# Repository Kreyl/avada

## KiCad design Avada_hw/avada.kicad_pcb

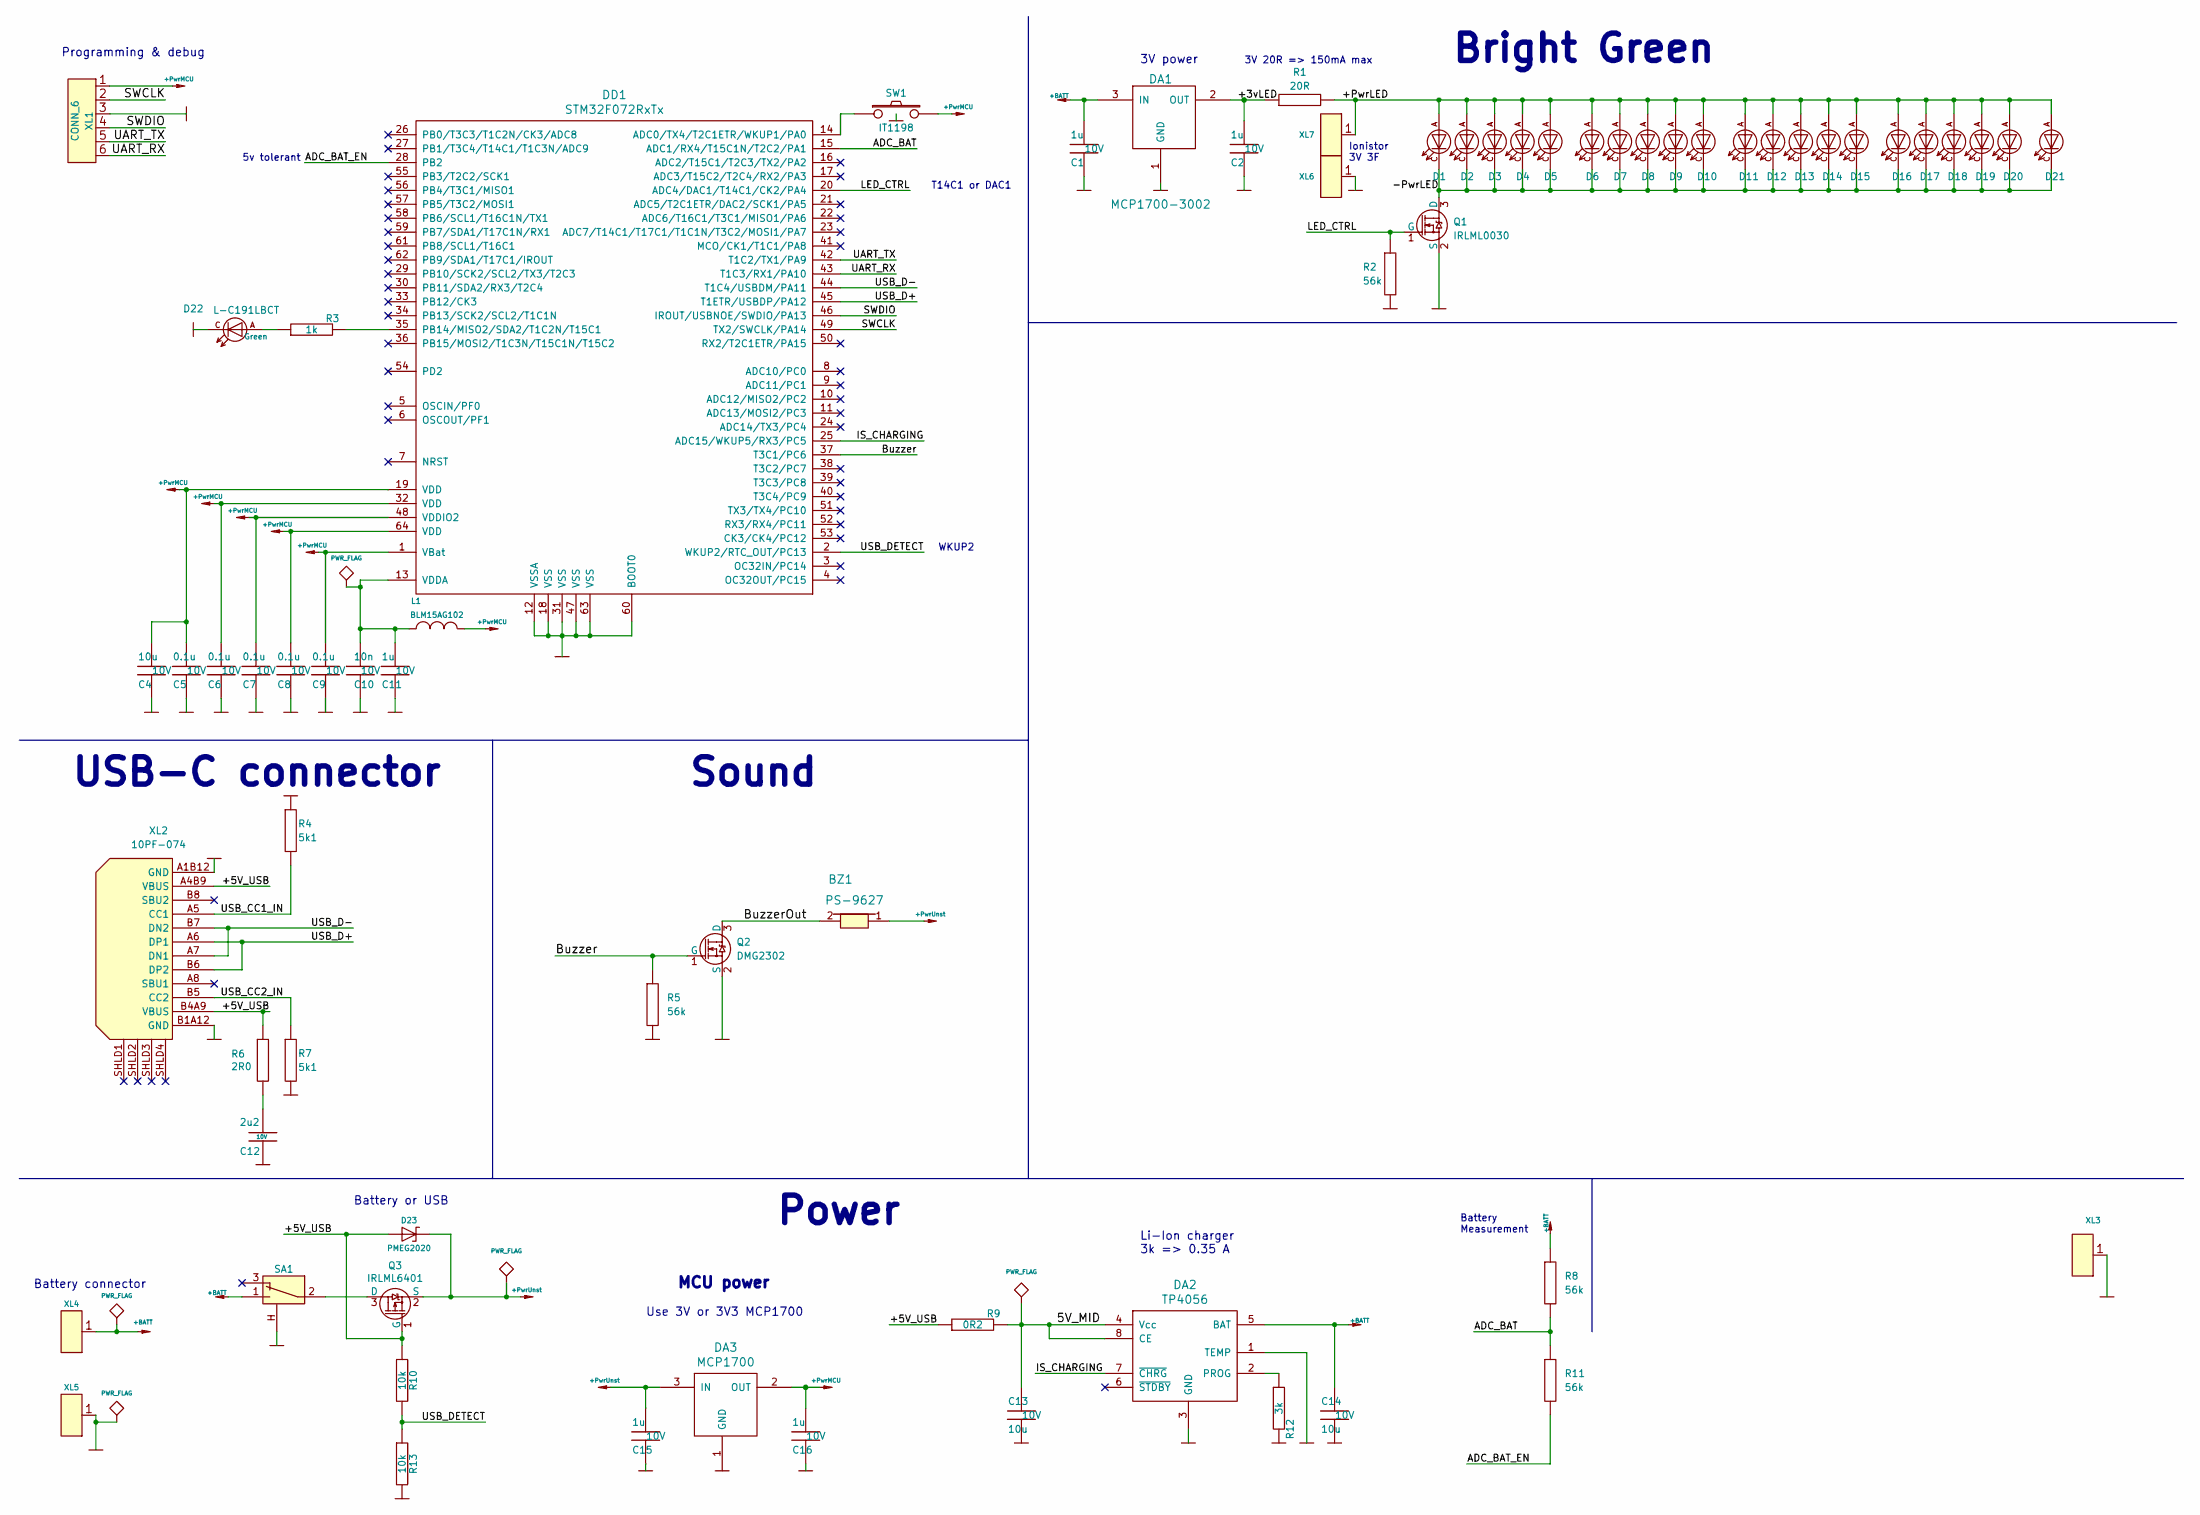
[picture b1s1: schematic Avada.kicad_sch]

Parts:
BZ1: PS-9627; BUZZER_HC0903
C1, C2, C11, C15, C16: 1u; CAP_0603_Silks; Tolerance 20%; Voltage 10V
C4, C13, C14: 10u; CAP_0603_Silks; Tolerance 20%; Voltage 10V
C5, C6, C7, C8, C9: 0.1u; CAP_0603_Silks; Tolerance 20%; Voltage 10V
C10: 10n; CAP_0603_Silks; Tolerance 20%; Voltage 10V
C12: 2u2; CAP_0603_Silks; Tolerance 20%; Voltage 10V
D1, D2, D3, D4, D5, D6, D7, D8, D9, D10, D11, D12, D13, D14, D15, D16, D17, D18, D19, D20, D21: 2835; LED_PLCC2835
D22: L-C191LBCT; LED_0603
D23: PMEG2020; SOD323
DA1: MCP1700-3002; SOT23-3A
DA2: TP4056; SO8_150MIL
DA3: MCP1700; SOT23-3A
DD1: STM32F072RxTx; LQFP64
L1: BLM15AG102; IND_0402; Tolerance 20%
Q1: IRLML0030; SOT23-3
Q2: DMG2302; SOT23-3
Q3: IRLML6401; SOT23-3
R1: 20R; RES_0603; Tolerance 1%
R2, R5, R8, R11: 56k; RES_0603; Tolerance 1%
R3: 1k; RES_0603; Tolerance 1%
R4, R7: 5k1; RES_0603; Tolerance 1%
R6: 2R0; RES_0603; Tolerance 1%
R9: 0R2; RES_1206; Tolerance 1%
R10, R13: 10k; RES_0603; Tolerance 1%
R12: 3k; RES_0603
SA1: SS-12F23; SW_SS-12F23
SW1: IT1198; BTN_IT1198
XL1: CONN_6; PLS-6
XL2: 10PF-074; USBC_10PF-074
XL3, XL5, XL6: CONN_1; PLS-1Square
XL4: CONN_1; PLS-1Oval
XL7: CONN_1; PLS-1Rnd

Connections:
+BATT: C1.1, C14.2, DA1.3 (IN), DA2.5 (BAT), R8.1, SA1.1, XL4.1
+PwrMCU: C4.1, C5.1, C6.1, C7.1, C8.1, C9.1, C16.1, DA3.2 (OUT), DD1.1 (VBat), DD1.19 (VDD), DD1.32 (VDD), DD1.48 (VDDIO2), DD1.64 (VDD), L1.1, SW1.2, XL1.1
+PwrUnst: BZ1.1, C15.1, D23.C, DA3.3 (IN), Q3.2 (S)
/5V_MID: C13.2, DA2.4 (Vcc), DA2.8 (CE), R9.2
/+3vLED: C2.1, DA1.2 (OUT), R1.1
/+5V_USB: D23.A, Q3.1 (G), R6.1, R9.1, R10.1, XL2.A4B9 (VBUS), XL2.B4A9 (VBUS)
/+PwrLED: D1.A, D2.A, D3.A, D4.A, D5.A, D6.A, D7.A, D8.A, D9.A, D10.A, D11.A, D12.A, D13.A, D14.A, D15.A, D16.A, D17.A, D18.A, D19.A, D20.A, D21.A, R1.2, XL7.1
/-PwrLED: D1.C, D2.C, D3.C, D4.C, D5.C, D6.C, D7.C, D8.C, D9.C, D10.C, D11.C, D12.C, D13.C, D14.C, D15.C, D16.C, D17.C, D18.C, D19.C, D20.C, D21.C, Q1.3 (D)
/ADC_BAT: DD1.15 (ADC1/RX4/T15C1N/T2C2/PA1), R8.2, R11.1
/ADC_BAT_EN: DD1.28 (PB2), R11.2
/Buzzer: DD1.37 (T3C1/PC6), Q2.1 (G), R5.1
/BuzzerOut: BZ1.2, Q2.3 (D)
/IS_CHARGING: DA2.7 (~CHRG), DD1.25 (ADC15/WKUP5/RX3/PC5)
/LED_CTRL: DD1.20 (ADC4/DAC1/T14C1/CK2/PA4), Q1.1 (G), R2.1
/SWCLK: DD1.49 (TX2/SWCLK/PA14), XL1.2
/SWDIO: DD1.46 (IROUT/USBNOE/SWDIO/PA13), XL1.4
/UART_RX: DD1.43 (T1C3/RX1/PA10), XL1.6
/UART_TX: DD1.42 (T1C2/TX1/PA9), XL1.5
/USB_CC1_IN: R4.2, XL2.A5 (CC1)
/USB_CC2_IN: R7.1, XL2.B5 (CC2)
/USB_D+: DD1.45 (T1ETR/USBDP/PA12), XL2.A6 (DP1), XL2.B6 (DP2)
/USB_D-: DD1.44 (T1C4/USBDM/PA11), XL2.A7 (DN1), XL2.B7 (DN2)
/USB_DETECT: DD1.2 (WKUP2/RTC_OUT/PC13), R10.2, R13.1
GND: C1.2, C2.2, C4.2, C5.2, C6.2, C7.2, C8.2, C9.2, C10.2, C11.2, C12.2, C13.1, C14.1, C15.2, C16.2, D22.C, DA1.1 (GND), DA2.1 (TEMP), DA2.3 (GND), DA3.1 (GND), DD1.12 (VSSA), DD1.18 (VSS), DD1.31 (VSS), DD1.47 (VSS), DD1.60 (BOOT0), DD1.63 (VSS), Q1.2 (S), Q2.2 (S), R2.2, R4.1, R5.2, R7.2, R12.2, R13.2, SA1.H, SW1.H, XL1.3, XL2.A1B12 (GND), XL2.B1A12 (GND), XL3.1, XL5.1, XL6.1
unnamed: C12.1, R6.2
unnamed: D22.A, R3.1
unnamed: DA2.2 (PROG), R12.1
unnamed: DD1.14 (ADC0/TX4/T2C1ETR/WKUP1/PA0), SW1.1
unnamed: DD1.35 (PB14/MISO2/SDA2/T1C2N/T15C1), R3.2
unnamed: C10.1, C11.1, DD1.13 (VDDA), L1.2
unnamed: Q3.3 (D), SA1.2

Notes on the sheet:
Battery connector
5v tolerant
Programming & debug
Use 3V or 3V3 MCP1700
Battery or USB
MCU power
Ionistor 3V 3F
3V power
Power
USB-C connector
T14C1 or DAC1
Bright Green
3V 20R => 150mA max
Battery Measurement
Li-Ion charger 3k => 0.35 A
WKUP2
Sound

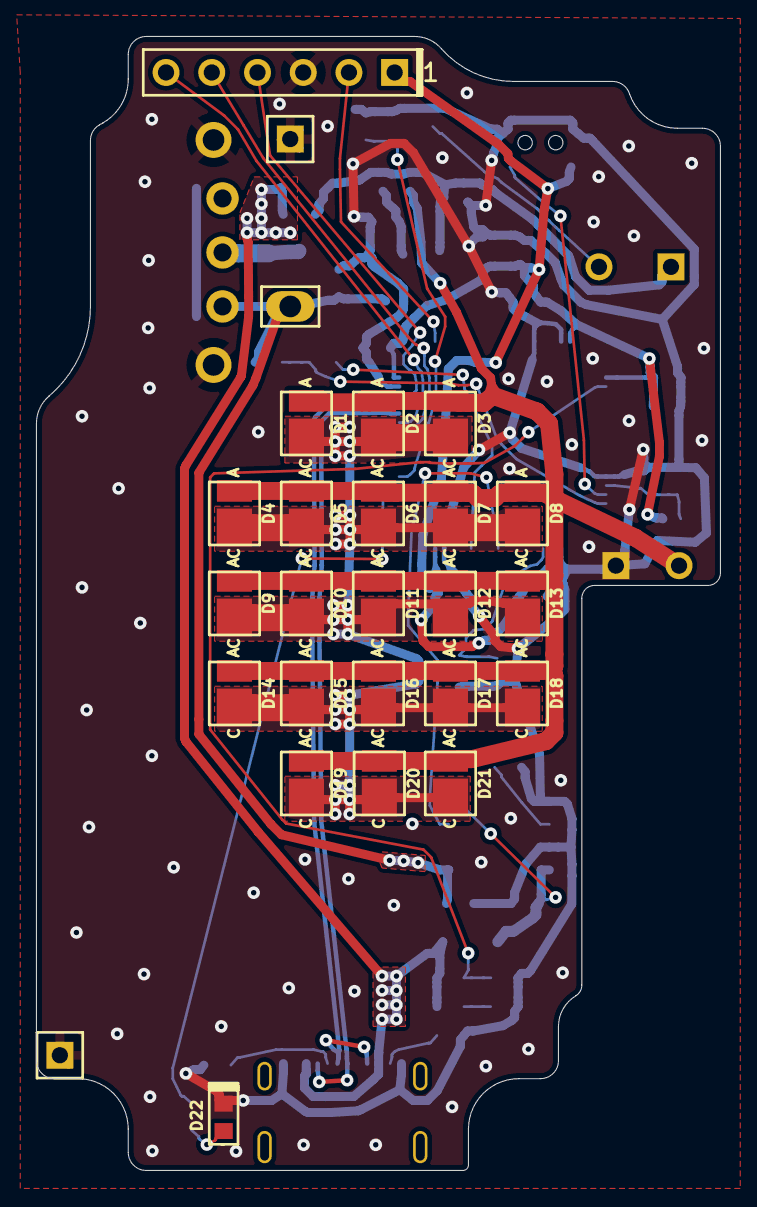
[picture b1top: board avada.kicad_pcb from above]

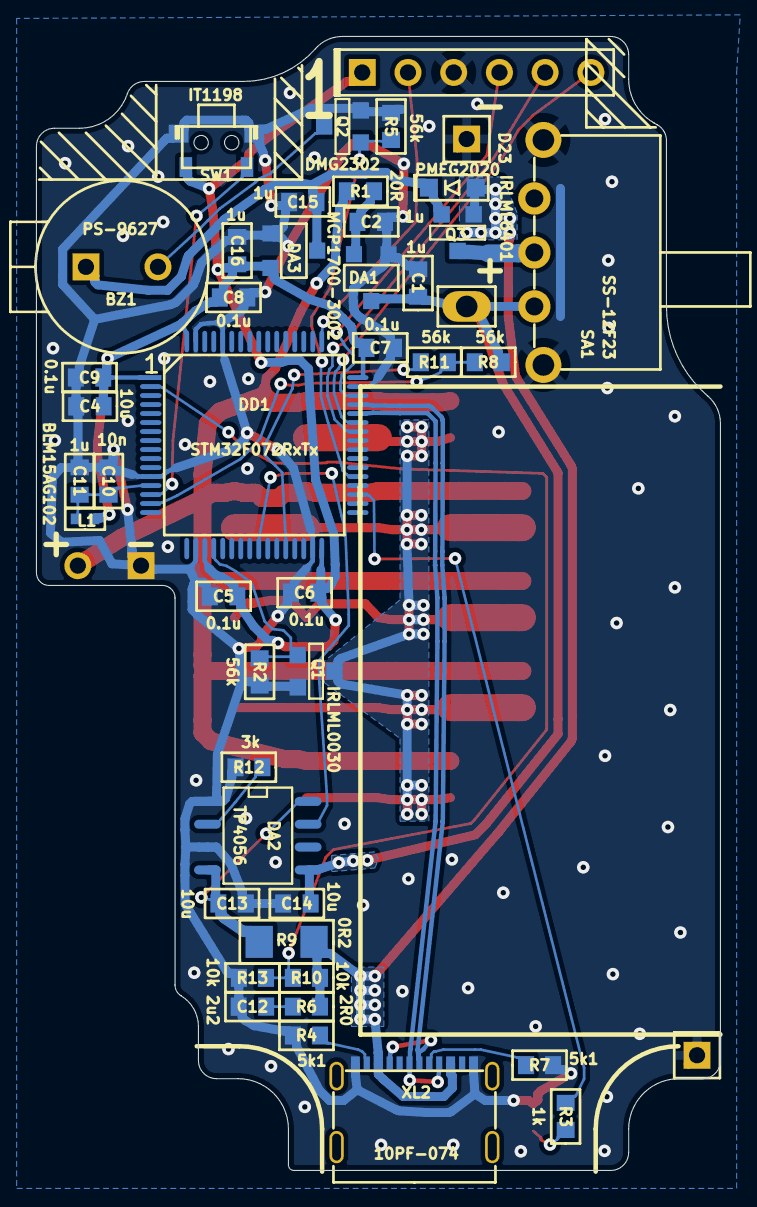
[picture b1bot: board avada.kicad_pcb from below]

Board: 2 copper layers, 38.0 x 63.0 mm, 69 parts (45 on the bottom side), 31 nets.

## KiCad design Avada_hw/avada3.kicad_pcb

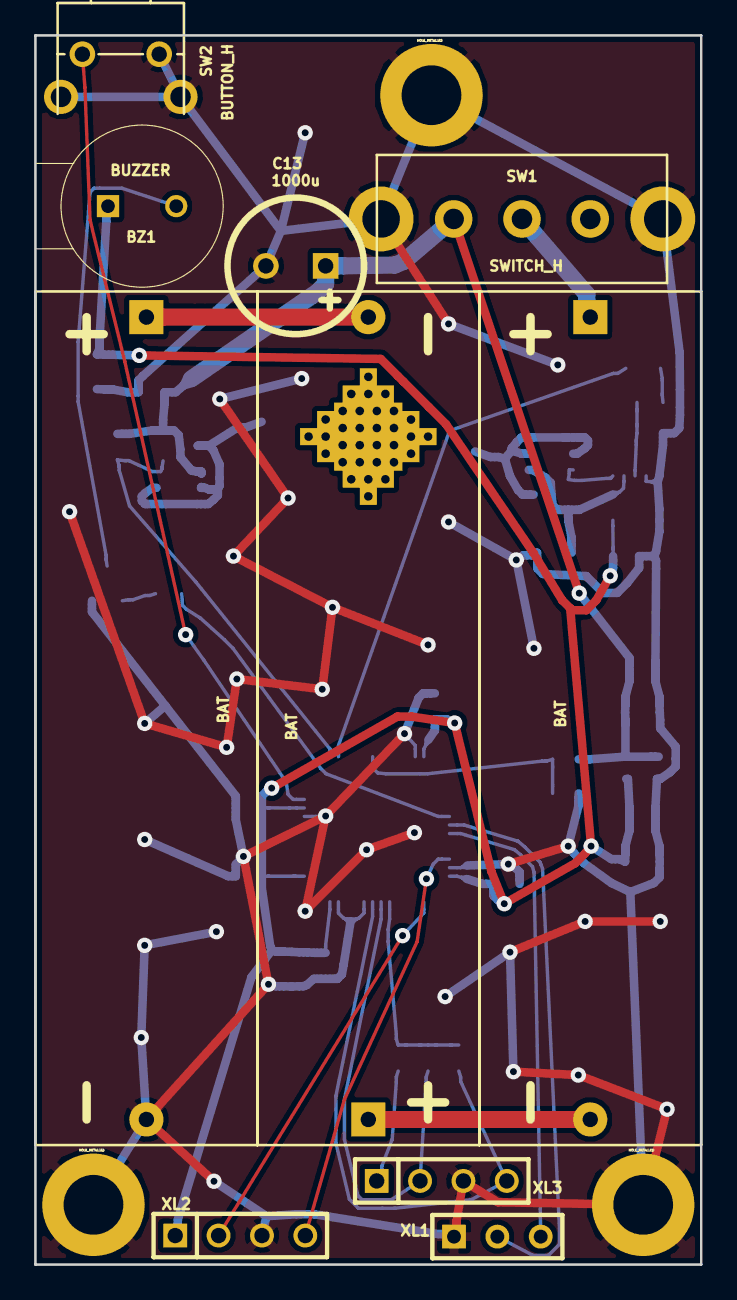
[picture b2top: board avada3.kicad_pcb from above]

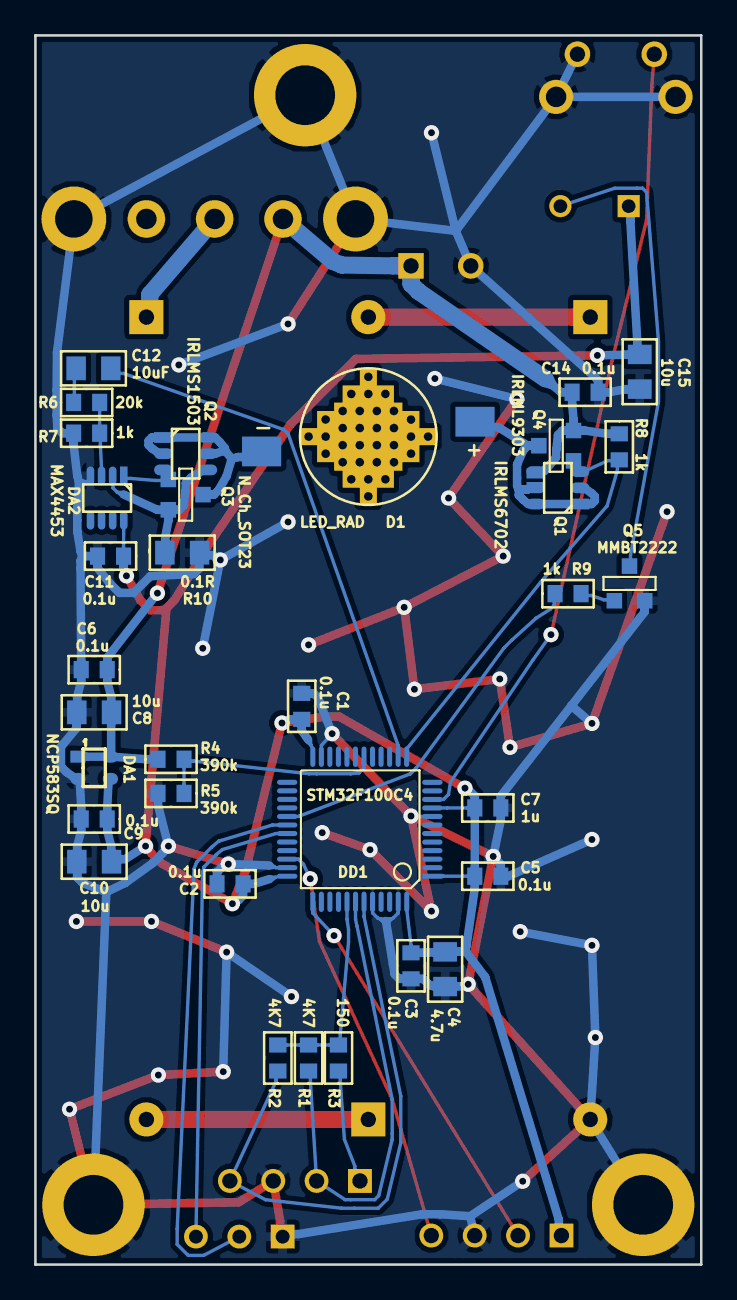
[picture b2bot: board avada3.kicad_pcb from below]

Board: 2 copper layers, 39.0 x 72.0 mm, 47 parts (34 on the bottom side), 27 nets.

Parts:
B1, B2, B3: BAT; BATTERY_AAA_X1
BZ1: BUZZER; BUZZER_HC0903
C1, C2, C3, C5, C6, C9, C11, C14: 0.1u; CAP_0603
C4: 4.7u; CAP_0805
C7: 1u; CAP_0603
C8, C10, C15: 10u; CAP_0805
C12: 10uF; CAP_0805
C13: 1000u; CAP_08xxR
D1: LED_RAD
DA1: NCP583SQ; SC82AB
DA2: MAX4453; SOT23-8
DD1: STM32F100C4; LQFP48
F1: FUSE0R; SOLDERFUSE
HOLE1, HOLE2, HOLE3: HOLE_METALLED; Hole3_5_out6mm
Q1: IRLMS6702; SOT23-6
Q2: IRLMS1503; SOT23-6
Q3: N_Ch_SOT23; SOT23
Q4: IRLML9303; SOT23
Q5: MMBT2222; SOT23
R1, R2: 4K7; RES_0603
R3: 150; RES_0603
R4, R5: 390k; RES_0603
R6: 20k; RES_0603
R7, R8, R9: 1k; RES_0603
R10: 0.1R; RES_0805
SW1: SWITCH_H; SWITCH_SS9
SW2: BUTTON_H; BUTTON_6x6_CORNER
XL1: CONN_3; SIL-3
XL2: ST_SWD; SIL-4
XL3: CONN_4; SIL-4

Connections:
+3.3V: BZ1.1, C1.1, C2.1, C3.1, C4.1, C5.2, C7.1, C9.1, C10.1, C11.1, C15.1, DA1.3, DA2.8, DD1.1, DD1.9, DD1.24, DD1.36, DD1.48, XL2.1
+BATT: C6.1, C8.1, C13.1, C14.1, DA1.1, DA1.4, F1.1, Q1.4, Q4.2, R4.1, R8.1, SW1.1
/BAT_IN: B3.A, SW1.2
/Buzzer: DD1.29, R9.1
/BuzzerOut: BZ1.2, Q5.3
/CURR_SNS: DA2.2, Q2.4, Q3.2, R10.1
/DAC: C12.1, DD1.14
/GreenEn: DD1.13, Q1.3, Q4.1, R8.2
/LED_A: D1.A, F1.2, Q1.1, Q1.2, Q1.5, Q1.6, Q4.3
/LED_C: D1.C, Q2.1, Q2.2, Q2.5, Q2.6, Q3.3
/P_SCL: DD1.42, R1.1, XL3.2
/P_SDA: DD1.43, R2.1, XL3.4
/PeriphPwr: DD1.41, R1.2, R2.2, R3.2
/PeriphPwr1: R3.1, XL3.1
/SWCLK: DD1.37, XL2.2
/SWDIO: DD1.34, XL2.4
/UART_RX: DD1.31, XL1.3
/UART_TX: DD1.30, XL1.2
/UBat/2: DD1.18, R4.2, R5.1
GND: B1.C, C1.2, C2.2, C3.2, C4.2, C5.1, C6.2, C7.2, C8.2, C9.2, C10.2, C11.2, C13.2, C14.2, C15.2, DA1.2, DA2.4, DD1.8, DD1.23, DD1.35, DD1.44, DD1.47, HOLE1.Hle, HOLE2.Hle, HOLE3.Hle, Q5.2, R5.2, R7.2, R10.2, SW1.H, SW2.2, SW2.H, XL1.1, XL2.3, XL3.3
unnamed: B1.A, B2.C
unnamed: Q5.1, R9.2
unnamed: C12.2, R6.1
unnamed: DD1.10, SW2.1
unnamed: B2.A, B3.C
unnamed: DA2.1, Q2.3, Q3.1
unnamed: DA2.3, R6.2, R7.1

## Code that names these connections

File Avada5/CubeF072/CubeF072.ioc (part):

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Mcu.Name=STM32F072R(8-B)Tx
Mcu.Package=LQFP64
Mcu.UserName=STM32F072R8Tx
PA0.Mode=SYS_WakeUp0
PA0.Signal=SYS_WKUP1
PA10.Mode=Asynchronous
PA10.Signal=USART1_RX
PA11.Mode=Device
PA11.Signal=USB_DM
PA12.Mode=Device
PA12.Signal=USB_DP
PA13.Mode=Serial_Wire
PA13.Signal=SYS_SWDIO
PA14.Mode=Serial_Wire
PA14.Signal=SYS_SWCLK
PA2.Mode=IN2
PA2.Signal=ADC_IN2
PA3.Mode=IN3
PA3.Signal=ADC_IN3
PA4.Signal=COMP_DAC1_group
PA9.Mode=Asynchronous
PA9.Signal=USART1_TX
PB14.Signal=S_TIM15_CH1
PC13.Mode=SYS_WakeUp1
PC13.Signal=SYS_WKUP2
PC5.Mode=SYS_WakeUp4
PC5.Signal=SYS_WKUP5
PC6.Signal=S_TIM3_CH1
RCC.SYSCLKFreq_VALUE=48000000
RCC.SYSCLKSource=RCC_SYSCLKSOURCE_HSI48
board=custom

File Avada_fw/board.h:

/*
 * board.h
 *
 *  Created on: 01.02.2017
 *      Author: Kreyl
 */

#pragma once

// ==== General ====
#define BOARD_NAME          "Avada6"
#define APP_NAME            "Avada"

// MCU type as defined in the ST header.
#define STM32F072xB     // no matter, 8 or B

// Freq of external crystal if any. Leave it here even if not used.
#define CRYSTAL_FREQ_HZ         12000000

// Ch timer
#define STM32_ST_IRQ_PRIORITY   2
#define STM32_ST_USE_TIMER      2
#define SYS_TIM_CLK             (Clk.APBFreqHz)

#define SIMPLESENSORS_ENABLED   TRUE
#define BUTTONS_ENABLED         FALSE
#define ADC_REQUIRED            FALSE
#define I2C1_ENABLED            FALSE
#define I2C_USE_SEMAPHORE       FALSE

#if 1 // ========================== GPIO =======================================
// PortMinTim_t: GPIO, Pin, Tim, TimChnl, invInverted, omPushPull, TopValue

// Buttons
#define BTN_PIN         GPIOA, 0, pudPullDown

// LEDs
#define LUMOS_PIN       { GPIOB, 14, TIM15, 1, invNotInverted, omPushPull, 255 }
#define GREEN_LED       GPIOA, 4

// Battery
#define IS_CHARGING     GPIOC, 5, pudPullUp

// Buzzer
#define BUZZER_PIN      GPIOC, 6, TIM3, 1, invNotInverted, omPushPull, 45

// UART
#define UART_GPIO       GPIOA
#define UART_TX_PIN     9
#define UART_RX_PIN     10

// USB
#define USB_DETECT_PIN  GPIOC, 13
#define USB_DM          GPIOA, 11
#define USB_DP          GPIOA, 12

#endif // GPIO

#if 1 // ========================== USB ========================================
#define USBDrv          USBD1   // USB driver to use

// CRS
#define CRS_PRESCALER   RCC_CRS_SYNC_DIV1
#define CRS_SOURCE      RCC_CRS_SYNC_SOURCE_USB
#define CRS_POLARITY    RCC_CRS_SYNC_POLARITY_RISING
#define CRS_RELOAD_VAL  ((48000000 / 1000) - 1) // Ftarget / Fsync - 1
#define CRS_ERROR_LIMIT 34
#define HSI48_CALIBRATN 32
#endif

#if 1 // =========================== DMA =======================================
#define STM32_DMA_REQUIRED  TRUE
// ==== Uart ====
#define UART_DMA_TX_MODE(Chnl) (STM32_DMA_CR_CHSEL(Chnl) | DMA_PRIORITY_LOW | STM32_DMA_CR_MSIZE_BYTE | STM32_DMA_CR_PSIZE_BYTE | STM32_DMA_CR_MINC | STM32_DMA_CR_DIR_M2P | STM32_DMA_CR_TCIE)
#define UART_DMA_RX_MODE(Chnl) (STM32_DMA_CR_CHSEL(Chnl) | DMA_PRIORITY_MEDIUM | STM32_DMA_CR_MSIZE_BYTE | STM32_DMA_CR_PSIZE_BYTE | STM32_DMA_CR_MINC | STM32_DMA_CR_DIR_P2M | STM32_DMA_CR_CIRC)
#define UART_DMA_TX     STM32_DMA_STREAM_ID(1, 2)
#define UART_DMA_RX     STM32_DMA_STREAM_ID(1, 3)
#define UART_DMA_CHNL   0   // Dummy

#if ADC_REQUIRED
#define ADC_DMA         STM32_DMA_STREAM_ID(1, 1)
#define ADC_DMA_MODE    STM32_DMA_CR_CHSEL(0) |   /* dummy */ \
                        DMA_PRIORITY_HIGH | \
                        STM32_DMA_CR_MSIZE_HWORD | \
                        STM32_DMA_CR_PSIZE_HWORD | \
                        STM32_DMA_CR_MINC |       /* Memory pointer increase */ \
                        STM32_DMA_CR_DIR_P2M |    /* Direction is peripheral to memory */ \
                        STM32_DMA_CR_TCIE         /* Enable Transmission Complete IRQ */
#endif // ADC

#endif // DMA

#if 1 // ========================== USART ======================================
#define PRINTF_FLOAT_EN FALSE
#define UART_TXBUF_SZ   2048
#define UART_RXBUF_SZ   512
#define CMD_BUF_SZ      256

#define CMD_UART        USART1


#define CMD_UART_PARAMS \
    CMD_UART, UART_GPIO, UART_TX_PIN, UART_GPIO, UART_RX_PIN, \
    UART_DMA_TX, UART_DMA_RX, UART_DMA_TX_MODE(UART_DMA_CHNL), UART_DMA_RX_MODE(UART_DMA_CHNL), \
    uartclkHSI // independent clock

#endif

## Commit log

2017-06-01 AVR-based Avada
2017-06-01 Avada2 with MANY btns
2017-06-01 Avada3
2017-06-01 Proceeding with sch
2017-06-02 + Avada4 sent to production
2017-06-07 + Firmware started
2017-06-07 + Buzzer works ok
2017-06-07 Removing not needed libs Last F030 code
2017-06-07 Switch to L151
2017-06-07 Flash ok
2017-08-08 Blink immediately, buzz after power-on
2018-04-04 + F100c4 LD
2018-04-04 Completing switch to L151 - DAC for older PCB version
2018-06-09 Switch to Atollic
2018-06-09 Back to new PCB, Release
2019-06-11 no message
2022-02-06 Smth unknown
2022-02-07 BlockSch
2022-04-08 UART and btn work
2022-04-08 + infoled Other in progress
2022-04-09 Working on ADC
2022-04-09 ADC works ok
2022-04-09 Current adjustment
2022-04-10 ILed adjustment works
2022-04-10 USB MSD works
2022-04-13 Before switching to thread
2022-04-13 Settings.ini is read
2022-04-14 Seems working
2022-04-15 Seems good. RC
2022-04-23 Charging LED is more intuitive
2023-05-28 Release
2023-06-14 Some renamings
2023-06-18 Sch seems done
2023-07-14 PCB Layout Started
2023-07-15 + PCB sent to factory
2023-08-21 Works
2023-08-21 Flash state machine and settings are rewritten for clarity
2023-08-21 Sleep timeout added
2023-08-26 Lumos made dim at start
